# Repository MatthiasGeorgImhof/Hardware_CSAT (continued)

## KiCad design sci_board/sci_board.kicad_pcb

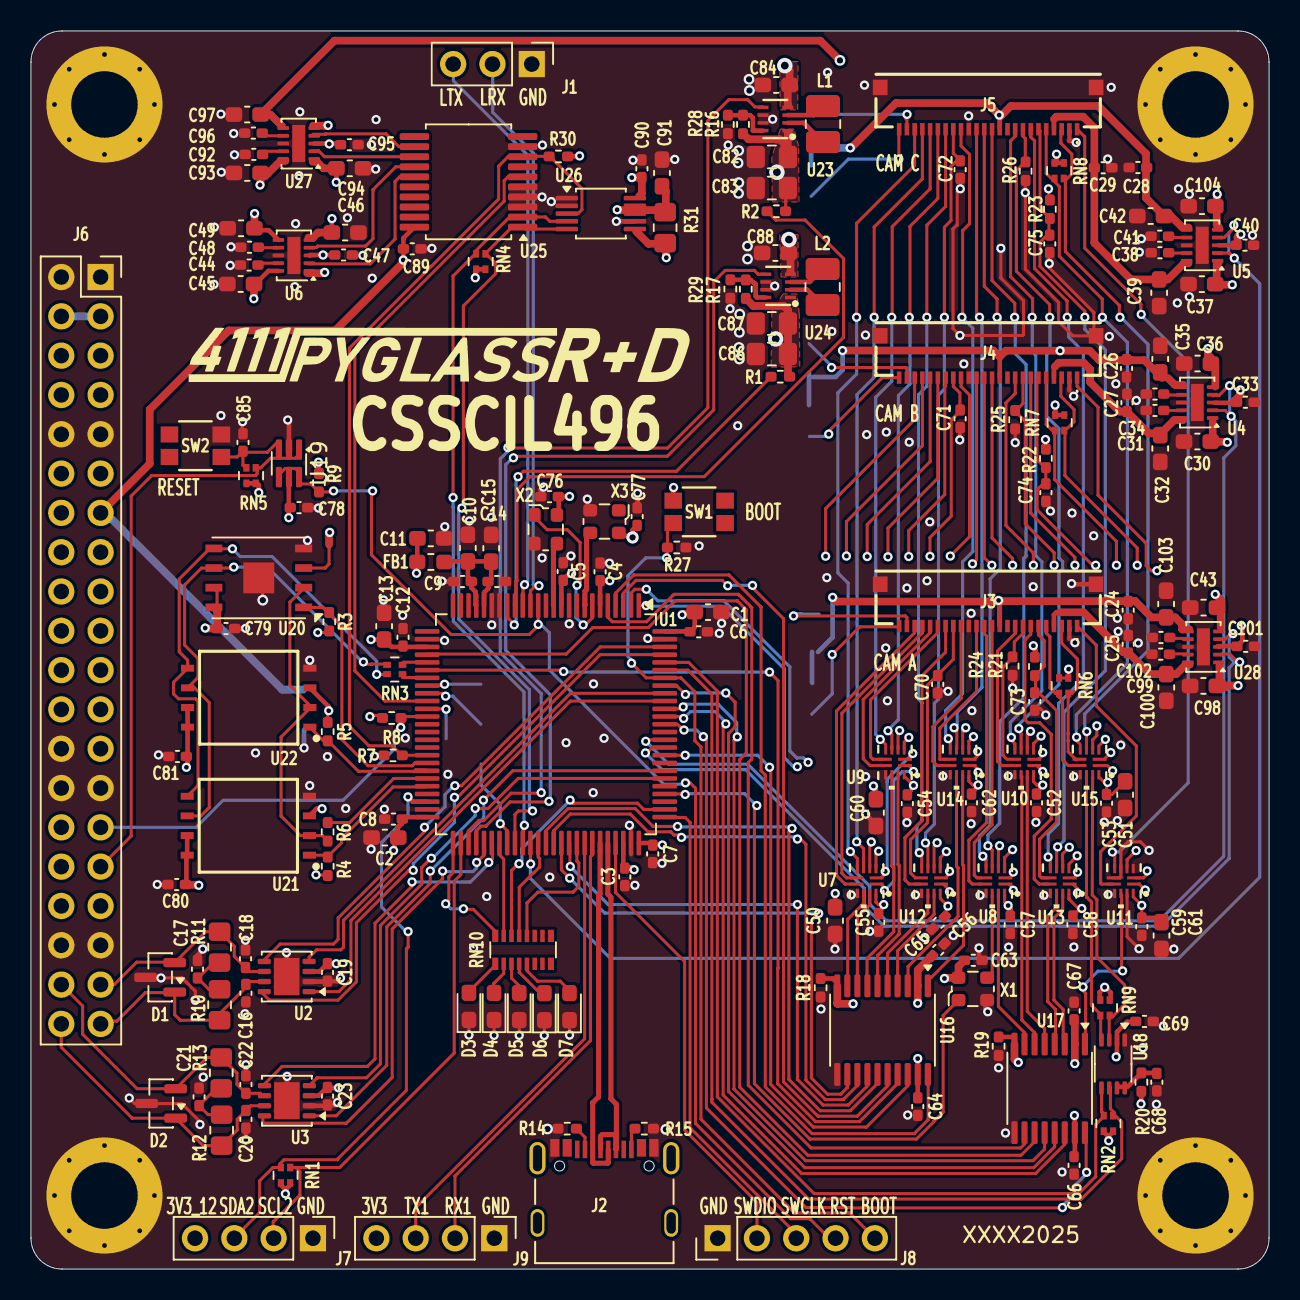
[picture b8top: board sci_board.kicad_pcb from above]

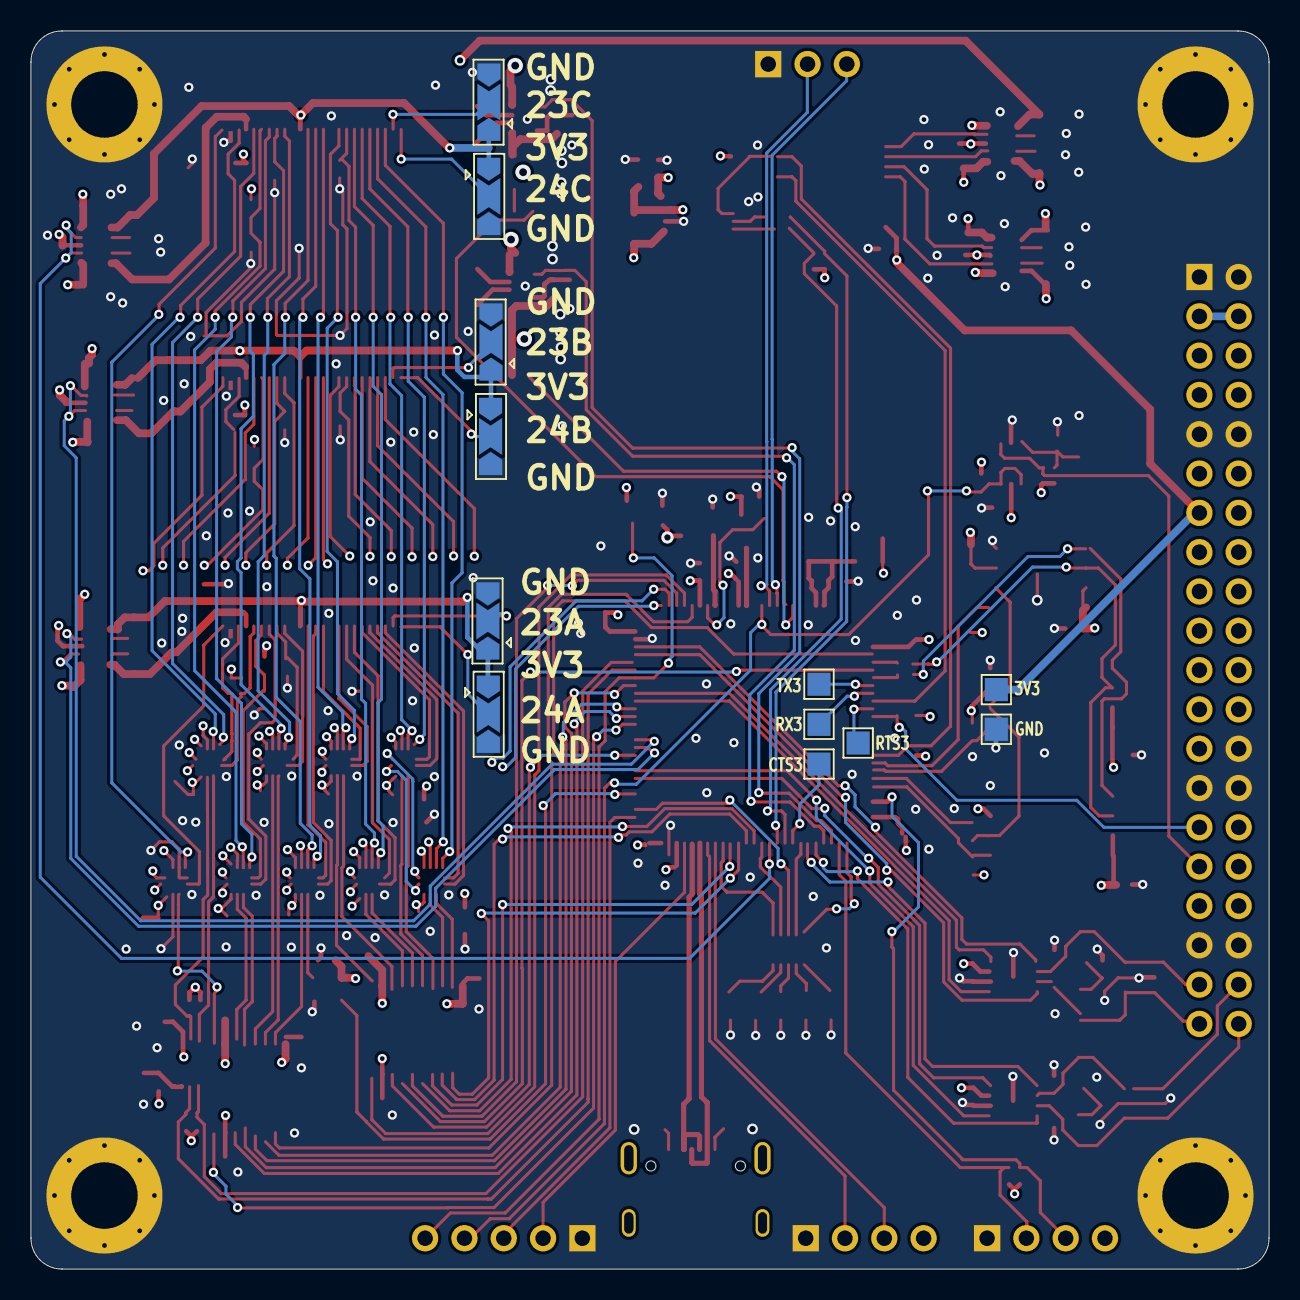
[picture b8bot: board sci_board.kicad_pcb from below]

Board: 4 copper layers, 80.0 x 80.0 mm, 216 parts (12 on the bottom side), 204 nets.

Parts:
C1, C2, C10, C11, C13, C15, C32, C35, C39, C42, C45, C49, C50, C51, C60, C61, C91, C93, C97, C100, C103: 10uF; C_0603_1608Metric_Pad1.08x0.95mm_HandSolder
C3, C4, C5, C6, C7, C8, C9, C12, C14, C19, C23, C24, C25, C26, C27, C28, C29, C33, C40, C47, C52, C53, C54, C55, C56, C57, C58, C59, C62, C63, C64, C65, C66, C67, C68, C69, C73, C74, C75, C76, C77, C78, C79, C80, C81, C85, C89, C90, C95, C101: 100nF; C_0402_1005Metric_Pad0.74x0.62mm_HandSolder
C16, C18, C20, C22: 100pF; C_0402_1005Metric_Pad0.74x0.62mm_HandSolder
C17, C21: 4nF7; C_0402_1005Metric_Pad0.74x0.62mm_HandSolder
C30, C36, C37, C43, C46, C84, C88, C94, C98, C104: 22uF; C_0603_1608Metric_Pad1.08x0.95mm_HandSolder
C31, C34, C38, C41, C44, C48, C92, C96, C99, C102: 220pF; C_0402_1005Metric_Pad0.74x0.62mm_HandSolder
C70, C71, C72: 22pF; C_0402_1005Metric_Pad0.74x0.62mm_HandSolder
C82, C83, C86, C87: 47uF; C_0805_2012Metric_Pad1.18x1.45mm_HandSolder
D1, D2: NUP2105LT1G; SOT-23
D3: RED; LED_0603_1608Metric_Pad1.05x0.95mm_HandSolder
D4: GREEN; LED_0603_1608Metric_Pad1.05x0.95mm_HandSolder
D5, D6, D7: YELLOW; LED_0603_1608Metric_Pad1.05x0.95mm_HandSolder
FB1: 120R; L_0603_1608Metric_Pad1.05x0.95mm_HandSolder
H1, H2, H3, H4: MountingHole_Pad; MountingHole_4.3mm_M4_Pad_Via_Custom
J1: Conn_01x03_Pin Vertical; PinHeader_1x03_P2.54mm_Vertical
J2: 10155435-00011LF; AMPHENOL_10155435-00011LF
J3, J4, J5: 10051922-2410EHLF; 100519222410EHLF
J6: PC104 Conn_02x20_Odd_Even; PinSocket_2x20_P2.54mm_Vertical
J7, J9: Conn_01x04_Pin Vertical; PinHeader_1x04_P2.54mm_Vertical
J8: Conn_01x05_Pin Vertical; PinHeader_1x05_P2.54mm_Vertical
JP1, JP2, JP3, JP4, JP5, JP6: SolderJumper_3_Open; SolderJumper-3_P2.0mm_Open_TrianglePad1.0x1.5mm
L1, L2: 1uH; L_1008_2520Metric_Pad1.43x2.20mm_HandSolder
NT1, NT2, NT3: NetTie_2; NetTie-2_SMD_Pad0.3mm
R1, R2: 10K; R_0402_1005Metric_Pad0.72x0.64mm_HandSolder
R3, R4, R5, R7, R9, R18, R19, R20, R21, R22, R23, R24, R25, R26, R27, R30: 100K; R_0402_1005Metric_Pad0.72x0.64mm_HandSolder
R6: 22R; R_0402_1005Metric_Pad0.72x0.64mm_HandSolder
R8: 330K; R_0402_1005Metric_Pad0.72x0.64mm_HandSolder
R10, R11, R12, R13: 60R4; R_0805_2012Metric_Pad1.20x1.40mm_HandSolder
R14, R15: 5K1; R_0402_1005Metric_Pad0.72x0.64mm_HandSolder
R16: 422K; R_0402_1005Metric_Pad0.72x0.64mm_HandSolder
R17: 237K; R_0402_1005Metric_Pad0.72x0.64mm_HandSolder
R28, R29: 91K; R_0402_1005Metric_Pad0.72x0.64mm_HandSolder
R31: 10m; R_0805_2012Metric_Pad1.20x1.40mm_HandSolder
RN1, RN2, RN4, RN6, RN7, RN8, RN9: 5K6; R_Array_Convex_2x0402_widepads
RN3: 22R; R_Array_Convex_2x0402_widepads
RN5: 100K; R_Array_Convex_2x0402_widepads
RN10: 1K; R_Array_Convex_8x0602_widepads
SW1, SW2: EVP-AA602W; EVP602AA
TP1: TX3; TestPoint_Pad_1.5x1.5mm
TP2: RX3; TestPoint_Pad_1.5x1.5mm
TP3: RTS3; TestPoint_Pad_1.5x1.5mm
TP4: CTS3; TestPoint_Pad_1.5x1.5mm
TP5: 3V3AUX; TestPoint_Pad_1.5x1.5mm
TP6: GND; TestPoint_Pad_1.5x1.5mm
U1: STM32L496VGTx; LQFP-100_14x14mm_P0.5mm
U2, U3: TCAN3414; VSON-8-1EP_3x3mm_P0.65mm_EP1.65x2.4mm
U4, U5, U6, U27, U28: TPS22968QDMGRQ1; WSON-10-1EP_2x3mm_P0.5mm_EP0.84x2.4mm
U7, U8, U9, U10, U11, U12, U13, U14, U15: TMUX131RMGR; VQFN12_RMG_TEX
U16: TXB0108PWR; TSSOP-20_4.4x6.5mm_P0.65mm
U17: TXB0106PWR; TSSOP-16_4.4x5mm_P0.65mm
U18: PCA9306DCUR; VSSOP-8_2.3x2mm_P0.5mm
U19: 74LVC2G07; SOT-363_SC-70-6
U20: MR25H10; DFN-8-1EP_6x5mm_P1.27mm_EP2x2mm
U21, U22: MT29F4G01ABAFDWB-IT:F TR; SON127P800X600X65-8N
U23, U24: TPS631000DRLR; TPS631000DRLR_TEX
U25: MCP23008T-E/SS; SSOP-20_5.3x7.2mm_P0.65mm
U26: INA226AIDGSR; VSSOP-10_3x3mm_P0.5mm
X1: 24MHz; Oscillator_SMD_ECS_2520MV-xxx-xx-4Pin_2.5x2.0mm
X2: 10MHz; Oscillator_SMD_ECS_2520MV-xxx-xx-4Pin_2.5x2.0mm
X3: 32.768KHZ; Oscillator_SMD_ECS_2520MV-xxx-xx-4Pin_2.5x2.0mm

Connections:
+3V3_AUX: C89.1, C90.1, J6.13, R30.1, R31.1, RN4.3 (R2.2), RN4.4 (R1.2), TP5.1, U25.20 (VDD), U26.6 (VS), U26.10 (IN+)
+3V3_STM32_Core: C1.2, C2.2, C3.1, C4.1, C5.1, C6.1, C7.1, C8.1, C11.1, C12.2, C13.2, C19.1, C23.1, C76.1, C77.1, C78.2, FB1.1, J6.14, J9.4, R7.1, R8.1, R9.1, RN5.1 (R1.1), RN5.2 (R2.1), SW1.1, U1.6 (VBAT), U1.11 (VDD), U1.28 (VDD), U1.50 (VDD), U1.73 (VDDUSB), U1.75 (VDD), U1.100 (VDD), U2.3 (VCC), U3.3 (VCC), U19.5 (VCC), X2.4 (VDD), X3.4 (VCC)
+BATT: C84.1, C88.1, J6.8, U23.4 (VIN), U24.4 (VIN)
/1V8: C36.1, C43.1, C63.1, C65.1, C67.1, C69.1, C86.1, C87.1, C104.1, R1.2, R17.1, R18.1, R19.1, RN9.3 (R2.2), RN9.4 (R1.2), U4.5 (VIN2), U5.5 (VIN2), U16.2 (VCCA), U16.10 (OE), U17.2 (VCCA), U17.8 (OE), U18.2 (VREF1), U24.1 (VOUT), U28.5 (VIN2), X1.4 (VDD)
/2V8: C30.1, C37.1, C82.1, C83.1, C98.1, R2.2, R16.1, U4.1 (VIN1), U5.1 (VIN1), U23.1 (VOUT), U28.1 (VIN1)
/3V3_Cameras: C33.1, C40.1, C50.1, C51.1, C52.1, C53.1, C54.1, C55.1, C56.1, C57.1, C58.1, C59.1, C60.1, C61.1, C62.1, C64.1, C66.1, C97.2, C101.1, R20.1, RN2.3 (R2.2), RN2.4 (R1.2), U4.3 (VBIAS), U5.3 (VBIAS), U7.12 (VDD), U8.12 (VDD), U9.12 (VDD), U10.12 (VDD), U11.12 (VDD), U12.12 (VDD), U13.12 (VDD), U14.12 (VDD), U15.12 (VDD), U16.19 (VCCB), U17.15 (VCCB), U27.6 (VOUT2), U28.3 (VBIAS)
/3V3_Flash: C49.2, C80.1, C81.1, R4.1, R5.1, U6.6 (VOUT2), U21.3 (WP#/IO2), U21.7 (HOLD#/IO3), U21.8 (VCC), U22.3 (WP#/IO2), U22.7 (HOLD#/IO3), U22.8 (VCC)
/3V3_Imager: C93.1, J7.4, RN1.3 (R2.2), RN1.4 (R1.2), U27.10 (VOUT1)
/3V3_MRAM: C45.1, C79.1, R3.1, U6.10 (VOUT1), U20.3 (~WP), U20.7 (~HOLD), U20.8 (VDD)
/ATTN: J6.29, R8.2, U1.37 (PB2)
/Aux Power Switch 3V3/ENABLE0: U25.12 (GP0), U27.4 (ON2)
/Aux Power Switch 3V3/ENABLE1: U25.13 (GP1), U27.2 (ON1)
/Aux Power Switch 3V3/ENABLE2: U6.4 (ON2), U25.14 (GP2)
/Aux Power Switch 3V3/ENABLE3: U6.2 (ON1), U25.15 (GP3)
/Aux Power Switch 3V3/RESET: U1.35 (PB0), U25.6 (*RESET)
/Aux Power Switch 3V3/VBUS: C46.1, C47.1, C91.1, C94.1, C95.1, R31.2, U6.1 (VIN1), U6.3 (VBIAS), U6.5 (VIN2), U26.8 (VBUS), U26.9 (IN-), U27.1 (VIN1), U27.3 (VBIAS), U27.5 (VIN2)
/CAN1_H: C20.1, D2.1 (K), J6.40, R12.1, U3.7 (CANH)
/CAN1_L: C22.2, D2.2 (K), J6.38, R13.2, U3.6 (CANL)
/CAN1_RX: U1.81 (PD0), U3.4 (RXD)
/CAN1_SHDN: U1.56 (PD9), U3.5 (SHTD)
/CAN1_STB: U1.55 (PD8), U3.8 (STB)
/CAN1_TX: U1.82 (PD1), U3.1 (TXD)
/CAN2_H: C16.1, D1.1 (K), J6.39, R10.1, U2.7 (CANH)
/CAN2_L: C18.2, D1.2 (K), J6.37, R11.2, U2.6 (CANL)
/CAN2_RX: U1.92 (PB6), U2.4 (RXD)
/CAN2_SHDN: U1.98 (PE1), U2.5 (SHTD)
/CAN2_STB: U1.97 (PE0), U2.8 (STB)
/CAN2_TX: U1.91 (PB5), U2.1 (TXD)
/Cameras/1V8_A: C24.1, C103.2, J3.11, JP1.1 (A), JP2.1 (A), R21.1, RN6.3 (R2.2), RN6.4 (R1.2), U28.6 (VOUT2)
/Cameras/1V8_B: C26.1, C35.2, J4.11, JP3.1 (A), JP4.1 (A), R22.1, RN7.3 (R2.2), RN7.4 (R1.2), U4.6 (VOUT2)
/Cameras/1V8_C: C28.1, C42.2, J5.11, JP5.1 (A), JP6.1 (A), R23.1, RN8.3 (R2.2), RN8.4 (R1.2), U5.6 (VOUT2)
/Cameras/2V8_A: C25.1, C100.1, J3.4, U28.10 (VOUT1)
/Cameras/2V8_B: C27.1, C32.1, J4.4, U4.10 (VOUT1)
/Cameras/2V8_C: C29.1, C39.1, J5.4, U5.10 (VOUT1)
/Cameras/*RESET_A: C73.1, J3.6, R21.2, U13.7 (S1A)
/Cameras/*RESET_B: C74.1, J4.6, R22.2, U13.3 (S1B)
/Cameras/*RESET_C: C75.1, J5.6, R23.2, U13.5 (S1C)
/Cameras/CLK_OE: U1.79 (PC11), X1.1 (TRI-STATE)
/Cameras/Camera_A/A_GND: J3.2, NT1.1
/Cameras/Camera_A/DCMI_02: J3.19, U9.7 (S1A)
/Cameras/Camera_A/DCMI_03: J3.21, U7.7 (S1A)
/Cameras/Camera_A/DCMI_04: J3.22, U7.8 (S2A)
/Cameras/Camera_A/DCMI_05: J3.20, U9.8 (S2A)
/Cameras/Camera_A/DCMI_06: J3.18, U12.8 (S2A)
/Cameras/Camera_A/DCMI_07: J3.16, U14.8 (S2A)
/Cameras/Camera_A/DCMI_08: J3.14, U14.7 (S1A)
/Cameras/Camera_A/DCMI_09: J3.12, U8.7 (S1A)
/Cameras/Camera_A/DCMI_HSYNC: J3.9, U10.8 (S2A)
/Cameras/Camera_A/DCMI_VSYNC: J3.7, U13.8 (S2A)
/Cameras/Camera_A/SCK: J3.5, RN6.1 (R1.1), U15.8 (S2A)
/Cameras/Camera_A/SDA: J3.3, RN6.2 (R2.1), U15.7 (S1A)
/Cameras/Camera_A/STROBE: J3.1, U11.8 (S2A)
/Cameras/Camera_A/XCLK: J3.13, U8.8 (S2A)
/Cameras/Camera_B/A_GND: J4.2, NT2.1
/Cameras/Camera_B/DCMI_02: J4.19, U9.3 (S1B)
/Cameras/Camera_B/DCMI_03: J4.21, U7.3 (S1B)
/Cameras/Camera_B/DCMI_04: J4.22, U7.4 (S2B)
/Cameras/Camera_B/DCMI_05: J4.20, U9.4 (S2B)
/Cameras/Camera_B/DCMI_06: J4.18, U12.4 (S2B)
/Cameras/Camera_B/DCMI_07: J4.16, U14.4 (S2B)
/Cameras/Camera_B/DCMI_08: J4.14, U14.3 (S1B)
/Cameras/Camera_B/DCMI_09: J4.12, U8.3 (S1B)
/Cameras/Camera_B/DCMI_HSYNC: J4.9, U10.4 (S2B)
/Cameras/Camera_B/DCMI_VSYNC: J4.7, U13.4 (S2B)
/Cameras/Camera_B/SCK: J4.5, RN7.1 (R1.1), U15.4 (S2B)
/Cameras/Camera_B/SDA: J4.3, RN7.2 (R2.1), U15.3 (S1B)
/Cameras/Camera_B/STROBE: J4.1, U11.4 (S2B)
/Cameras/Camera_B/XCLK: J4.13, U8.4 (S2B)
/Cameras/Camera_C/A_GND: J5.2, NT3.1
/Cameras/Camera_C/DCMI_02: J5.19, U9.5 (S1C)
/Cameras/Camera_C/DCMI_03: J5.21, U7.5 (S1C)
/Cameras/Camera_C/DCMI_04: J5.22, U7.6 (S2C)
/Cameras/Camera_C/DCMI_05: J5.20, U9.6 (S2C)
/Cameras/Camera_C/DCMI_06: J5.18, U12.6 (S2C)
/Cameras/Camera_C/DCMI_07: J5.16, U14.6 (S2C)
/Cameras/Camera_C/DCMI_08: J5.14, U14.5 (S1C)
/Cameras/Camera_C/DCMI_09: J5.12, U8.5 (S1C)
/Cameras/Camera_C/DCMI_HSYNC: J5.9, U10.6 (S2C)
/Cameras/Camera_C/DCMI_VSYNC: J5.7, U13.6 (S2C)
/Cameras/Camera_C/SCK: J5.5, RN8.1 (R1.1), U15.6 (S2C)
/Cameras/Camera_C/SDA: J5.3, RN8.2 (R2.1), U15.5 (S1C)
/Cameras/Camera_C/STROBE: J5.1, U11.6 (S2C)
/Cameras/Camera_C/XCLK: J5.13, U8.6 (S2C)
/Cameras/DCMI_00: U1.63 (PC6), U16.15 (B5)
/Cameras/DCMI_01: U1.64 (PC7), U16.13 (B7)
/Cameras/DCMI_02: U1.65 (PC8), U16.12 (B8)
/Cameras/DCMI_03: U1.66 (PC9), U16.14 (B6)
/Cameras/DCMI_04: U1.3 (PE4), U16.16 (B4)
/Cameras/DCMI_05: U1.84 (PD3), U16.18 (B2)
/Cameras/DCMI_06: U1.4 (PE5), U16.20 (B1)
/Cameras/DCMI_07: U1.5 (PE6), U17.10 (B6)
/Cameras/DCMI_HSYNC: U1.29 (PA4), U17.11 (B5)
/Cameras/DCMI_PLXCLK: U1.31 (PA6), U16.17 (B3)
/Cameras/DCMI_PLXCLK_A: C70.1, J3.17, U12.7 (S1A)
/Cameras/DCMI_PLXCLK_B: C71.1, J4.17, U12.3 (S1B)
/Cameras/DCMI_PLXCLK_C: C72.1, J5.17, U12.5 (S1C)
/Cameras/DCMI_VSYNC: U1.93 (PB7), U17.13 (B3)
/Cameras/ENABLE_1V8: U1.54 (PB15), U24.5 (EN)
/Cameras/ENABLE_2V8: U1.53 (PB14), U23.5 (EN)
/Cameras/ENABLE_A: U1.85 (PD4), U28.2 (ON1), U28.4 (ON2)
/Cameras/ENABLE_B: U1.86 (PD5), U4.2 (ON1), U4.4 (ON2)
/Cameras/ENABLE_C: U1.61 (PD14), U5.2 (ON1), U5.4 (ON2)
/Cameras/Multiplexer/DCMI_00: U9.11 (D1), U16.6 (A5)
/Cameras/Multiplexer/DCMI_01: U7.11 (D1), U16.8 (A7)
/Cameras/Multiplexer/DCMI_02: U7.10 (D2), U16.9 (A8)
/Cameras/Multiplexer/DCMI_03: U9.10 (D2), U16.7 (A6)
/Cameras/Multiplexer/DCMI_04: U12.10 (D2), U16.5 (A4)
/Cameras/Multiplexer/DCMI_05: U14.10 (D2), U16.3 (A2)
/Cameras/Multiplexer/DCMI_06: U14.11 (D1), U16.1 (A1)
/Cameras/Multiplexer/DCMI_07: U8.11 (D1), U17.7 (A6)
/Cameras/Multiplexer/DCMI_HSYNC: U10.10 (D2), U17.6 (A5)
/Cameras/Multiplexer/DCMI_PLXCLK: U12.11 (D1), U16.4 (A3)
/Cameras/Multiplexer/DCMI_VSYNC: U13.10 (D2), U17.4 (A3)
/Cameras/Multiplexer/I2C_SCK: RN9.1 (R1.1), U15.10 (D2), U18.4 (SDA1)
/Cameras/Multiplexer/I2C_SDA: RN9.2 (R2.1), U15.11 (D1), U18.3 (SCL1)
/Cameras/Multiplexer/PWRDN: U10.11 (D1), U17.5 (A4)
/Cameras/Multiplexer/RESET: U13.11 (D1), U17.3 (A2)
/Cameras/Multiplexer/STROBE: U11.10 (D2), U17.1 (A1)
/Cameras/PWRDN: U1.90 (PB4), U17.12 (B4)
/Cameras/PWRDN_A: J3.8, R24.1, U10.7 (S1A)
/Cameras/PWRDN_B: J4.8, R25.1, U10.3 (S1B)
/Cameras/PWRDN_C: J5.8, R26.1, U10.5 (S1C)
/Cameras/Power Regulator 1V8/LX1: L2.2, U24.3 (LX1)
/Cameras/Power Regulator 1V8/LX2: L2.1, U24.2 (LX2)
/Cameras/Power Regulator 1V8/R-: R17.2, R29.1, U24.8 (FB)
/Cameras/Power Regulator 2V8/LX1: L1.2, U23.3 (LX1)
/Cameras/Power Regulator 2V8/LX2: L1.1, U23.2 (LX2)
/Cameras/Power Regulator 2V8/R-: R16.2, R28.1, U23.8 (FB)
/Cameras/RESET: U1.89 (PB3), U17.14 (B2)
/Cameras/S0: U1.1 (PE2), U7.1 (SEL0), U8.1 (SEL0), U9.1 (SEL0), U10.1 (SEL0), U11.1 (SEL0), U12.1 (SEL0), U13.1 (SEL0), U14.1 (SEL0), U15.1 (SEL0)
/Cameras/S1: U1.2 (PE3), U7.2 (SEL1), U8.2 (SEL1), U9.2 (SEL1), U10.2 (SEL1), U11.2 (SEL1), U12.2 (SEL1), U13.2 (SEL1), U14.2 (SEL1), U15.2 (SEL1)
/Cameras/STROBE: U1.88 (PD7), U17.16 (B1)
/Cameras/XCLK: U8.10 (D2), X1.3 (OUTPUT)
/Flash1/SPI_CLK: RN3.1 (R1.1), U20.6 (SCK), U21.6 (SCK), U22.6 (SCK)
/Flash1/SPI_MISO: R6.2, U20.2 (SO), U21.2 (SO/IO1), U22.2 (SO/IO1)
/Flash1/SPI_MOSI: RN3.2 (R2.1), U20.5 (SI), U21.5 (SI/IO0), U22.5 (SI/IO0)
/I2C1_SCK: RN2.1 (R1.1), U1.95 (PB8), U18.6 (SCL2)
/I2C1_SDA: RN2.2 (R2.1), U1.96 (PB9), U18.5 (SDA2)
/I2C2_SCK: J7.2, RN1.1 (R1.1), U1.52 (PB13)
/I2C2_SDA: J7.3, RN1.2 (R2.1), U1.48 (PB11)
/I2C4_SCK: RN4.1 (R1.1), U1.59 (PD12), U25.1 (SCL), U26.5 (SCL)
/I2C4_SDA: RN4.2 (R2.1), U1.60 (PD13), U25.2 (SDA), U26.4 (SDA)
/INTERBOARD CONNECTOR/BATT: J6.3, J6.4
/PMIC/ADC3_IN3: R2.1, U1.17 (PC2)
/PMIC/ADC3_IN4: R1.1, U1.18 (PC3)
/PMIC/BOOT0: J8.5, R27.1, SW1.2, U1.94 (PH3)
/PMIC/LED1: RN10.16 (R), U1.51 (PB12)
/PMIC/LED2: RN10.15 (R), U1.57 (PD10)
/PMIC/LED3: RN10.14 (R), U1.77 (PA15)
/PMIC/LED4: RN10.13 (R), U1.62 (PD15)
/PMIC/LED5: RN10.12 (R), U1.67 (PA8)
/PMIC/LPUART_RX: J1.2, U1.15 (PC0)
/PMIC/LPUART_TX: J1.3, U1.16 (PC1)
/PMIC/NRST: J8.4, R9.2, U1.14 (NRST), U19.4 (OUT2), U19.6 (OUT1)
/PMIC/OSC32_IN: U1.8 (PC14), X3.3 (OUT)
/PMIC/OSC_HSE_IN: U1.12 (PH0), X2.3 (OUTPUT)
/PMIC/OSC_HSE_OE: U1.7 (PC13), X2.1 (TRI-STATE)
/PMIC/RESET: C85.1, RN5.4 (R1.2), SW2.3, U19.3 (IN2)
/PMIC/SPI1_MISO: R6.1, U1.45 (PE14)
/PMIC/SPI1_MOSI: RN3.3 (R2.2), U1.32 (PA7)
/PMIC/SPI1_SCK: RN3.4 (R1.2), U1.30 (PA5)
/PMIC/SWCLK: J8.3, U1.76 (PA14)
/PMIC/SWDIO: J8.2, U1.72 (PA13)
/PMIC/USART1_RX: J9.2, U1.69 (PA10)
/PMIC/USART1_TX: J9.3, U1.68 (PA9)
/PMIC/USART3_CTS: TP4.1, U1.58 (PD11)
/PMIC/USART3_RTS: TP3.1, U1.36 (PB1)
/PMIC/USART3_RX: TP2.1, U1.34 (PC5)
/PMIC/USART3_TX: TP1.1, U1.33 (PC4)
/PMIC/USB_OTG_FS_DM: J2.A7 (DN1_A), J2.B7 (DN2_B), U1.70 (PA11)
/PMIC/USB_OTG_FS_DP: J2.A6 (DP1_A), J2.B6 (DP2_B), U1.71 (PA12)
/PMIC/VDDA: C9.1, C10.1, C14.2, C15.2, FB1.2, U1.21 (VREF+), U1.22 (VDDA)
/Power_INT: R7.2, R30.2, U1.42 (PE11), U25.8 (INT), U26.3 (ALERT)
/SCI_RESET: J6.31, RN5.3 (R2.2), U19.1 (IN1)
/SPI1_CS_FLASH1: R4.2, U1.46 (PE15), U21.1 (CS#)
/SPI1_CS_FLASH2: R5.2, U1.44 (PE13), U22.1 (CS#)
/SPI1_CS_MRAM: R3.2, U1.43 (PE12), U20.1 (~CS)
GND: C1.1, C2.1, C3.2, C4.2, C5.2, C6.2, C7.2, C8.2, C9.2, C10.2, C11.2, C12.1, C13.1, C14.1, C15.1, C16.2, C17.2, C18.1, C19.2, C20.2, C21.2, C22.1, C23.2, C24.2, C25.2, C26.2, C27.2, C28.2, C29.2, C30.2, C31.2, C32.2, C33.2, C34.1, C35.1, C36.2, C37.2, C38.2, C39.2, C40.2, C41.1, C42.1, C43.2, C44.2, C45.2, C46.2, C47.2, C48.1, C49.1, C50.2, C51.2, C52.2, C53.2, C54.2, C55.2, C56.2, C57.2, C58.2, C59.2, C60.2, C61.2, C62.2, C63.2, C64.2, C65.2, C66.2, C67.2, C68.2, C69.2, C70.2, C71.2, C72.2, C73.2, C74.2, C75.2, C76.2, C77.2, C78.1, C79.2, C80.2, C81.2, C82.2, C83.2, C84.2, C85.2, C86.2, C87.2, C88.2, C89.2, C90.2, C91.2, C92.2, C93.2, C94.2, C95.2, C96.1, C97.1, C98.2, C99.2, C100.2, C101.2, C102.1, C103.1, C104.2, D1.3 (A), D2.3 (A), D3.1 (K), D4.1 (K), D5.1 (K), D6.1 (K), D7.1 (K), H1.1, H2.1, H3.1, H4.1, J1.1, J2.A1_B12 (GND), J2.B1_A12 (GND__1), J3.15, J3.MP1, J3.MP2, J4.15, J4.MP1, J4.MP2, J5.15, J5.MP1, J5.MP2, J6.1, J6.2, J6.9, J6.10, J6.26, J6.27, J6.28, J6.35, J6.36, J7.1, J8.1, J9.1, JP1.3 (B), JP2.3 (B), JP3.3 (B), JP4.3 (B), JP5.3 (B), JP6.3 (B), NT1.2, NT2.2, NT3.2, R14.1, R15.1, R18.2, R19.2, R24.2, R25.2, R26.2, R27.2, R28.2, R29.2, SW2.4, TP6.1, U1.10 (VSS), U1.19 (VSSA), U1.20 (VREF-), U1.27 (VSS), U1.49 (VSS), U1.74 (VSS), U1.99 (VSS), U2.2 (GND), U2.9 (GND), U3.2 (GND), U3.9 (GND), U4.8 (GND), U4.11 (TPAD), U5.8 (GND), U5.11 (TPAD), U6.8 (GND), U6.11 (TPAD), U7.9 (GND), U8.9 (GND), U9.9 (GND), U10.9 (GND), U11.3 (S1B), U11.5 (S1C), U11.7 (S1A), U11.9 (GND), U11.11 (D1), U12.9 (GND), U13.9 (GND), U14.9 (GND), U15.9 (GND), U16.11 (GND), U17.9 (GND), U18.1 (GND), U19.2 (GND), U20.4 (VSS), U20.9 (PAD), U21.4 (VSS), U22.4 (VSS), U23.6 (MODE), U23.7 (GND), U24.6 (MODE), U24.7 (GND), U25.3 (A2), U25.4 (A1), U25.5 (A0), U25.9 (VSS), U26.1 (A1), U26.2 (A0), U26.7 (GND), U27.8 (GND), U27.11 (TPAD), U28.8 (GND), U28.11 (TPAD), X1.2 (GND), X2.2 (GND), X3.2 (GND)
unnamed: C17.1, R10.2, R11.1
unnamed: C21.1, R12.2, R13.1
unnamed: D3.2 (A), RN10.1 (R)
unnamed: D4.2 (A), RN10.2 (R)
unnamed: D5.2 (A), RN10.3 (R)
unnamed: D6.2 (A), RN10.4 (R)
unnamed: D7.2 (A), RN10.5 (R)
unnamed: J2.A5 (CC1_A), R14.2
unnamed: J2.B5 (CC2_B), R15.2
unnamed: J3.23, JP1.2 (C)
unnamed: J3.24, JP2.2 (C)
unnamed: J4.23, JP3.2 (C)
unnamed: J4.24, JP4.2 (C)
unnamed: J5.23, JP5.2 (C)
unnamed: J5.24, JP6.2 (C)
unnamed: C31.1, U4.9 (CT1)
unnamed: C34.2, U4.7 (CT2)
unnamed: C38.1, U5.9 (CT1)
unnamed: C41.2, U5.7 (CT2)
unnamed: C44.1, U6.9 (CT1)
unnamed: C48.2, U6.7 (CT2)
unnamed: C68.1, R20.2, U18.7 (VREF2), U18.8 (EN)
unnamed: C92.1, U27.9 (CT1)
unnamed: C96.2, U27.7 (CT2)
unnamed: C99.1, U28.9 (CT1)
unnamed: C102.2, U28.7 (CT2)

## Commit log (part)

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2024-08-13 clone, point submodule to MGI, correct case of AVIONICS_BOARD-cache.lib
2024-08-25 cleaning up the master branch for correctness with KICAD 8
2024-08-25 full project (eps, av, rf) with main connector changed to 2x48. av and rf have footprint 80x80mm
2024-08-25 change form factor to 80x80 and cleanup pcb
2024-08-26 add second CAN bus and USB
2024-08-30 avionics board with CAN bus 3.3 to 5V generation
2024-08-30 turning off warnings, clean up K8 errors
2024-09-02 EPS: cleaning up, footprint to 80x80, and replace discrete switches with ICs for switch and measurement
2024-09-02 AV: small cleanup, USB, and CAN power
2024-09-02 version with all enables to CPU
2024-09-02 combine interrupts per powerline and use i2c expanders to turn on and solicit feedback
2024-09-03 need to cleanup enables, int and positions
2024-09-07 laying all the tracks, interim commit
2024-09-07 interim commit
2024-09-08 schema and pcb are listing no errors anymore. warnings mostly related to silkscreen
2024-09-08 link battery to bus through switch, INA226 on I2C, and level shifter between vbat and MCU
2024-09-08 cleanup silk screens
2024-09-08 cleanup schema in preparation of pin reassignments
2024-09-09 use all interrupts
2024-09-10 add 2V8 regulator and switch for SCI cameras, refactor switch/monitors with nonstandard voltage that require level shifting
2024-09-11 RSQ chip replaced with dual nor gates chips
2024-09-12 connect all parallel solar panels to mcu
2024-09-13 reconcile av board with eps changes
2024-09-13 cleanup avionics boards after remapping connector
2024-09-14 flip CAN high low around to ease access from the front side
2024-09-14 align with submodules
2024-09-14 beginning the AUX board for power and CAN bridging
2024-09-15 aux board: use active FTI chip FT230X that has all the functionality needed TX RX RTS CTS
2024-09-16 starting the SCI board with triple camera multiplexing
2024-09-16 draft of science board: add USB and thermal imager, sort out power switches for cameras
2024-09-16 SCI board: add flash and mram; decorate PMC with boot, reset, etc
2024-09-16 start SCI pcb
2024-09-18 cameras have fcp connectors, use data 2:9, and need a clock
2024-09-18 begin to update the pcb
2024-09-19 continue layout
2024-09-20 replace big multiplexers with tiny ones, replace boost converters with true ones
2024-09-21 changed over SCI to smaller footprint switches
2024-09-21 replace nearly all buck converters with boost buck (missing is 5raw
2024-09-21 final version with 48 pin connector: all boost/buck converters, 2 switched batt lines (though not connected to bus yet
2024-09-22 changed from 48 pin connector to 40 pic PCA connector. remove uarts, ensure reset pins for all system components, attention pin to iniate IRQ on all components
2024-09-22 create common STEP folder
2024-09-22 AUX to PCI104
2024-09-22 SCI is based on PC104 connector
2024-09-22 AVI module is PCI104 compatible
2024-09-23 temporary branch for radio to pc104
2024-09-24 create Common global libraries for footprints and symbols
2024-09-24 rf module is pc104 compatible
2024-09-27 simply eps and automate startup conditions
2024-09-28 EPS refactored without 5V and changed pc104, no missing connections. Still needs checking and silkmask
2024-09-28 pcb and silk screen cleanup, interim
2024-09-28 error and warning free pcb
2024-09-29 0.5mm wide power lanes
2024-09-29 push PC104 bus reorder (no more 5V, 20 lines of 3V3 and 4 switched batt) to system components
2024-09-30 light sensors with i2c multiplexers for AVI board. i2c amp/volt meter for attitude control coils
2024-10-01 assign can power to core powerm will need to use GPIO to enable power stndby from MCUs, finalize pc104 bus assignments
2024-10-02 openlst board
2024-10-02 replacd TJA1042 with TCAN3414 that allows differential from 3V, negating the need for 5V generator
2024-10-02 openlst: replacd TJA1042 with TCAN3414 that allows differential from 3V, negating the need for 5V generator
2024-10-03 create and check BOM, check MC pinout, CAN standby and shutdown for each channel
2024-10-04 remove submodule for openlst-hw, make it part of this repo'
2024-10-04 SCI BOM updated
2024-10-04 reduce some R to 0402 for consistency with imported components
2024-10-04 interim checkin before streamlining AVI
2024-10-05 refactor AVI into nicer hierarchical components
2024-10-05 AVI assigning interrupts
2024-10-05 reconcile BOMS for AVI. SCI and AUX
2024-10-05 cleaning out project detritus
2024-10-05 RF board BOM
2024-10-05 interim checkin for EPS BOM
2024-10-05 minor cleanup of OST RF board, remove resistor and capacitor from oscillator output
2024-10-05 complete BOM assignment for EPS, next step circular check and deep dives
2024-10-06 consistency between the different boards
2024-10-06 add decorations and labels to PCBs
2024-10-06 add decorations and labels to PCBs part 2
2024-10-07 reenumerate AVI board
2024-10-19 use small connectors in corners and on sides for sun sensors and solar cells
2024-10-25 detailed power switches moved from EPS to invidual boards, each board only has core and aux bus (and batt if needed) which scales better. Reassign PC104 slots
2024-10-28 AUX ready for build SCI: changed camera power switches because the original ones cannot handle voltage below 2.5, we have 1.8!
2024-10-30 checking AUX and SCI, tweak BOM
2024-10-31 check BOM and footprints for SCI and AUX
2024-11-01 finalize boards for fabrication: SCI and AUX
2024-11-01 AUX SCI ordered version
2024-11-02 SCI power switch: change I2C expander to manufacturer recommended footprint to enable production with PCBWAY
2025-05-11 full science board with camera switches
2025-05-11 cleanup and bom
2025-05-12 update aux board to kicad 9: fix USB UART 2 TWO pin switches
2025-05-16 AVI board simplified and cleaned up
2025-05-16 via - pad distance rules for SCI and AVI
2025-05-25 EPS board update: single side assembly, <200 components
2025-05-25 EPS and AVI joint cleanup
2025-05-25 SCI AVI and EPS are consistent again
2025-05-26 SCI AVI and EPS are now consistent
2025-05-30 rework COM board, add SPI ethernet for sat modem, upgrade all projects to 9.0.2
2025-05-30 first version of sci wo switches
2025-05-31 bom for SCI
2025-05-31 EPS AVI SCI SCIwoSwitches RF AUX all updated to use RNs. BOMs completed
2025-06-01 sorting out pullups on resets and attention. replace reset with RN where possible. Introduce CN to save some parts
2025-06-02 cleanup pullups for reset and schmitt trigger for reset; select available thermal NTCs for avi board and use chip for voltage dividers
2025-06-06 checked BOM for sci wo switches
2025-06-06 BOM avi checked
2025-06-07 cleanup AVI board mag torque traces
2025-06-07 cleanup avionics
2025-06-08 EPS needs flash to self update with bootloader
2025-06-08 power traces and vias of AUX and SCIlite are 0,5mm and 0.5/1.0mm
2025-06-08 reconcile suite
2025-06-08 move SPI CS pullups to outer schema to combine multiple with RNs
2025-06-11 06102025 SCI lite and AVI
2025-06-12 interim checkin
2025-06-12 06112025 SCI lite and AVI
2025-06-12 all projects satisfy custom rule of min pad spacing 0.2mm to satisfy pcbway constraints
2025-08-09 EPS board add RTC battery
2025-08-10 add STP for CR2450
2025-08-10 add pictures for readmes
2025-08-10 comm board png
2025-08-12 move project to new location, update sympbol, footprint and step paths
2025-10-20 VRef+ meeds to be connected to VDDA, should not be left floating
2025-10-20 cleanup VAAD traces
2026-03-24 SCI bodge board to correct I2C switching
2026-03-25 Comm board update with CC1101 and CC1090 on 915MHz
2026-03-26 house cleaning: remove openlst
2026-03-26 move commonly used hierarchical sheets to common/sheets for easy reuse
2026-03-26 absolute paths for includes of includes or the second level common/sheet will cause problems!
2026-03-27 move legacy schema and files into inactive folders for removal
2026-03-27 moving common sheets to common, cleanup for some missed files
2026-03-27 licensing terms
2026-03-27 cleaning up common sheets and projects. prepare for removal of legacy path links
2026-04-05 splyglass logos
2026-06-08 Initial clean YouTube version of the CubeStack boards
